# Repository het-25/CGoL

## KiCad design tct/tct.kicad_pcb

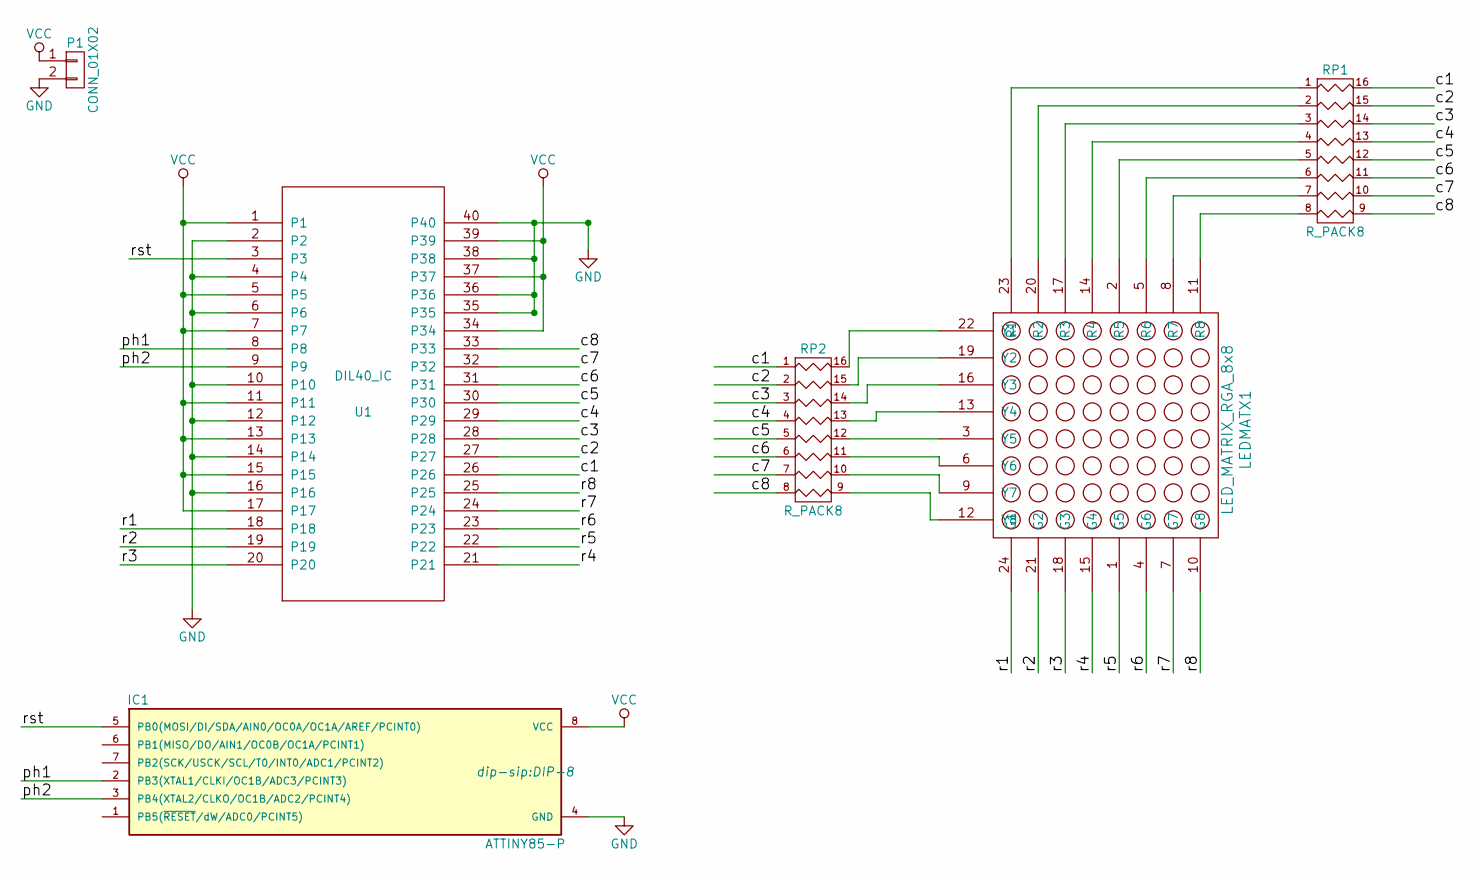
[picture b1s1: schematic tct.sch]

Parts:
IC1: ATTINY85-P; DIP-8
LEDMATX1: LED_MATRIX_RGA_8x8; LED_MATRIX_RG_8x8
P1: CONN_01X02; Pin_Header_Straight_1x02
RP1, RP2: R_PACK8; R_Array_Convex_8x0602
U1: DIL40_IC; DIP-40

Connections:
/c1: RP1.16 (R1), RP2.1, U1.26
/c2: RP1.15 (R2), RP2.2, U1.27
/c3: RP1.14 (R3), RP2.3, U1.28
/c4: RP1.13 (R4), RP2.4, U1.29
/c5: RP1.12 (R5), RP2.5, U1.30
/c6: RP1.11 (R6), RP2.6, U1.31
/c7: RP1.10 (R7), RP2.7, U1.32
/c8: RP1.9 (R8), RP2.8, U1.33
/ph1: IC1.2 (PB3(XTAL1/CLKI/OC1B/ADC3/PCINT3)), U1.8
/ph2: IC1.3 (PB4(XTAL2/CLKO/OC1B/ADC2/PCINT4)), U1.9
/r1: LEDMATX1.24 (G1), U1.18
/r2: LEDMATX1.21 (G2), U1.19
/r3: LEDMATX1.18 (G3), U1.20
/r4: LEDMATX1.15 (G4), U1.21
/r5: LEDMATX1.1 (G5), U1.22
/r6: LEDMATX1.4 (G6), U1.23
/r7: LEDMATX1.7 (G7), U1.24
/r8: LEDMATX1.10 (G8), U1.25
/rst: IC1.5 (PB0(MOSI/DI/SDA/AIN0/OC0A/OC1A/AREF/PCI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), U1.3
GND: IC1.4 (GND), P1.2, U1.2, U1.4, U1.6, U1.10, U1.12, U1.14, U1.16, U1.35, U1.36, U1.38, U1.40
unnamed: LEDMATX1.2 (R5), RP1.5
unnamed: LEDMATX1.3 (Y5), RP2.12 (R5)
unnamed: LEDMATX1.5 (R6), RP1.6
unnamed: LEDMATX1.6 (Y6), RP2.11 (R6)
unnamed: LEDMATX1.8 (R7), RP1.7
unnamed: LEDMATX1.9 (Y7), RP2.10 (R7)
unnamed: LEDMATX1.11 (R8), RP1.8
unnamed: LEDMATX1.12 (Y8), RP2.9 (R8)
unnamed: LEDMATX1.13 (Y4), RP2.13 (R4)
unnamed: LEDMATX1.14 (R4), RP1.4
unnamed: LEDMATX1.16 (Y3), RP2.14 (R3)
unnamed: LEDMATX1.17 (R3), RP1.3
unnamed: LEDMATX1.19 (Y2), RP2.15 (R2)
unnamed: LEDMATX1.20 (R2), RP1.2
unnamed: LEDMATX1.22 (Y1), RP2.16 (R1)
unnamed: LEDMATX1.23 (R1), RP1.1
VCC: IC1.8 (VCC), P1.1, U1.1, U1.5, U1.7, U1.11, U1.13, U1.15, U1.17, U1.34, U1.37, U1.39

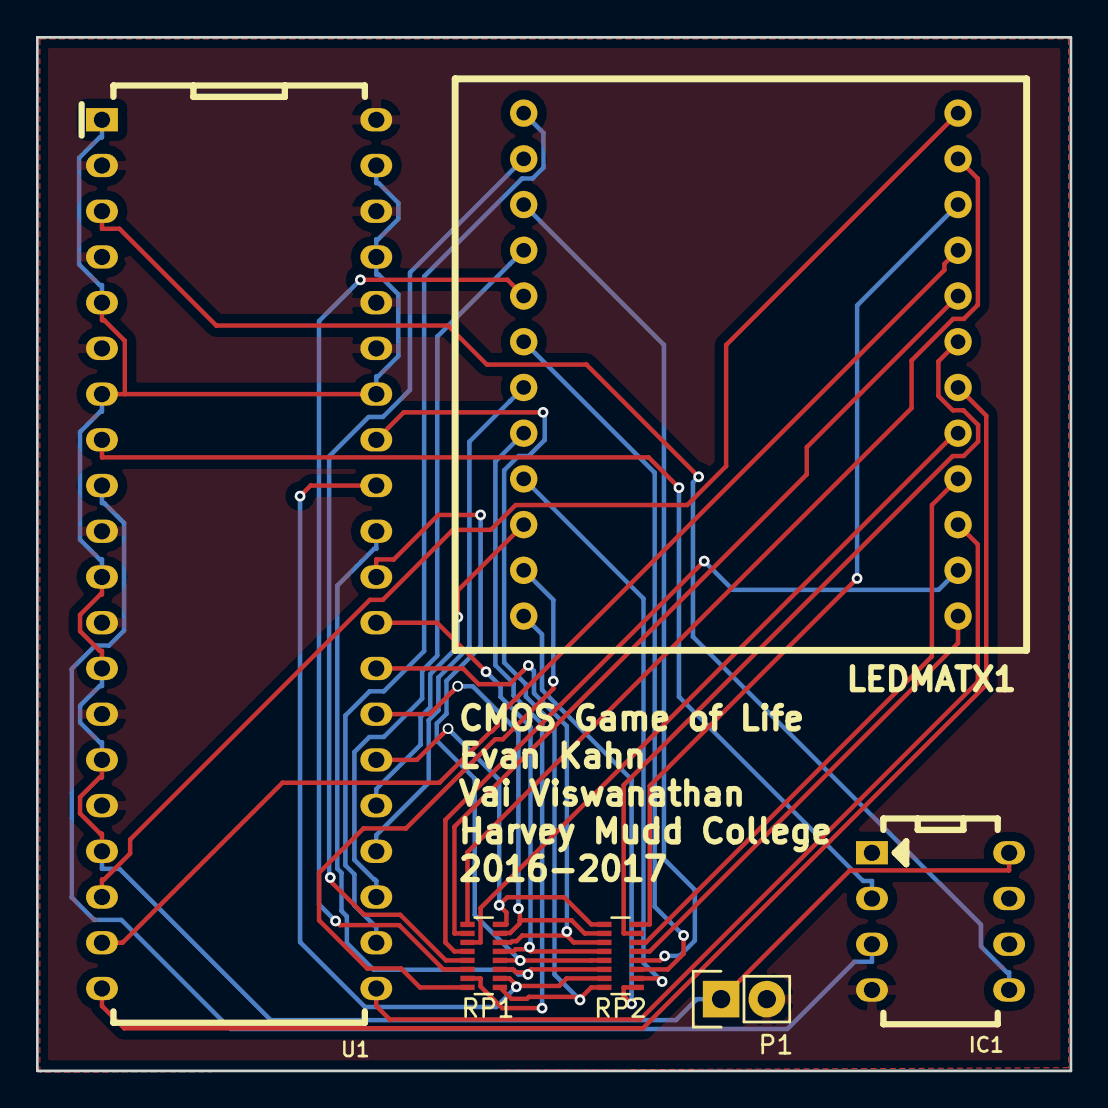
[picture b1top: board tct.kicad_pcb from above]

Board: 2 copper layers, 57.4 x 57.4 mm, 6 parts (0 on the bottom side), 37 nets.

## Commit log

2016-03-18 uploaded mips.sv why not
2016-03-18 added some code
2016-03-18 Created current state register file
2016-03-18 stuff
2016-03-19 tentative controller
2016-03-19 Created top level module for decoder
2016-03-19 updated for 3-bit address register
2016-03-20 Created current state register file module
2016-03-20 decoder testbench and testvectors
2016-03-20 more testvectors for decoder; hopefully LED driver works
2016-03-21 now it compiles at least
2016-03-22 Created top-level module CGOL
2016-03-22 made some stuff compile
2016-03-22 Populated entire top-level structure
2016-03-22 prev_state\
2016-03-22 new testvectors
2016-03-22 updated gitignore
2016-03-22 testbench_curren.sv
2016-03-22 created testbench for current state rf
2016-03-22 prev_test
2016-03-23 Updated all files from desktop
2016-03-23 added more testbenches
2016-03-23 testvectors
2016-03-23 ready for prototyping
2016-03-23 prototyping
2016-03-23 clocking
2016-03-23 changed timings and stuff
2016-03-27 Updated to version simulating with testbench
2016-03-27 Made some changes
    - Testbench not simulating with combinational LED decoder
2016-03-27 Updated testvectors for combination LED decoder
2016-03-27 Merge branch 'master' into fpga_prototype
    # Conflicts:
    # assorted_modules.sv
    # cgol.sv
    # current_state.sv
    # prev_state.sv
    # testbench_overall.sv
2016-03-27 CGOL still simulates
2016-03-27 UPdated to flops
    - does not simulate
2016-03-28 ayo fixed some shtuff
2016-03-28 Changed display decoder back to sequential
    We can go back to combinational and save a lot of chip space if we don't
    need to be perfectionists though I guess.
2016-03-28 added synthesized verilog
    i’m done 4 2nite
2016-03-28 Renamed vars in prev_state
2016-03-28 added all_synth autogenerated schematic file
2016-03-28 Added all of the code to "Everything.sv"
2016-03-29 testvector generator done
    to run: python testvector_gen.py > out.tv
2016-03-29 added WORK library
2016-03-29 added testvector file
2016-03-29 updated modelsim for new testvector
2016-03-29 updated project files
2016-03-29 Edited sorted_modules and everything to compile
2016-03-29 added new all_synth_syn
2016-03-29 added all_synth schematic
2016-03-29 added all_synth hopefully
2016-03-29 fixed everything.sv
2016-03-29 added new current_state
2016-03-29 made current_State synchronous
2016-03-30 added current_state synthed with modified verilog??
2016-03-30 added 8 bit mux (not tested, but checks out ok)
2016-03-30 oops i did it again
2016-03-30 added updated current state registers
2016-03-30 tried it again
2016-03-30 added working current_state register
2016-03-30 removed double address argument on current/next state registers
2016-03-30 moved some files around
2016-03-30 cleanup cleanup
    everybody cleanup
2016-03-31 added full all_synth
2016-03-31 ok updated new library
2016-03-31 fixed
2016-03-31 commited new currentstate library
2016-04-05 folded current_state into all_synth
    woo
2016-04-06 included finished all_synth layout
2016-04-11 multiple starting configurations (not working yet)
2016-04-11 fixt
    now it simulates w multiple start configurations
2016-04-11 line
    i accidentally one
2018-03-19 Added pcb files
